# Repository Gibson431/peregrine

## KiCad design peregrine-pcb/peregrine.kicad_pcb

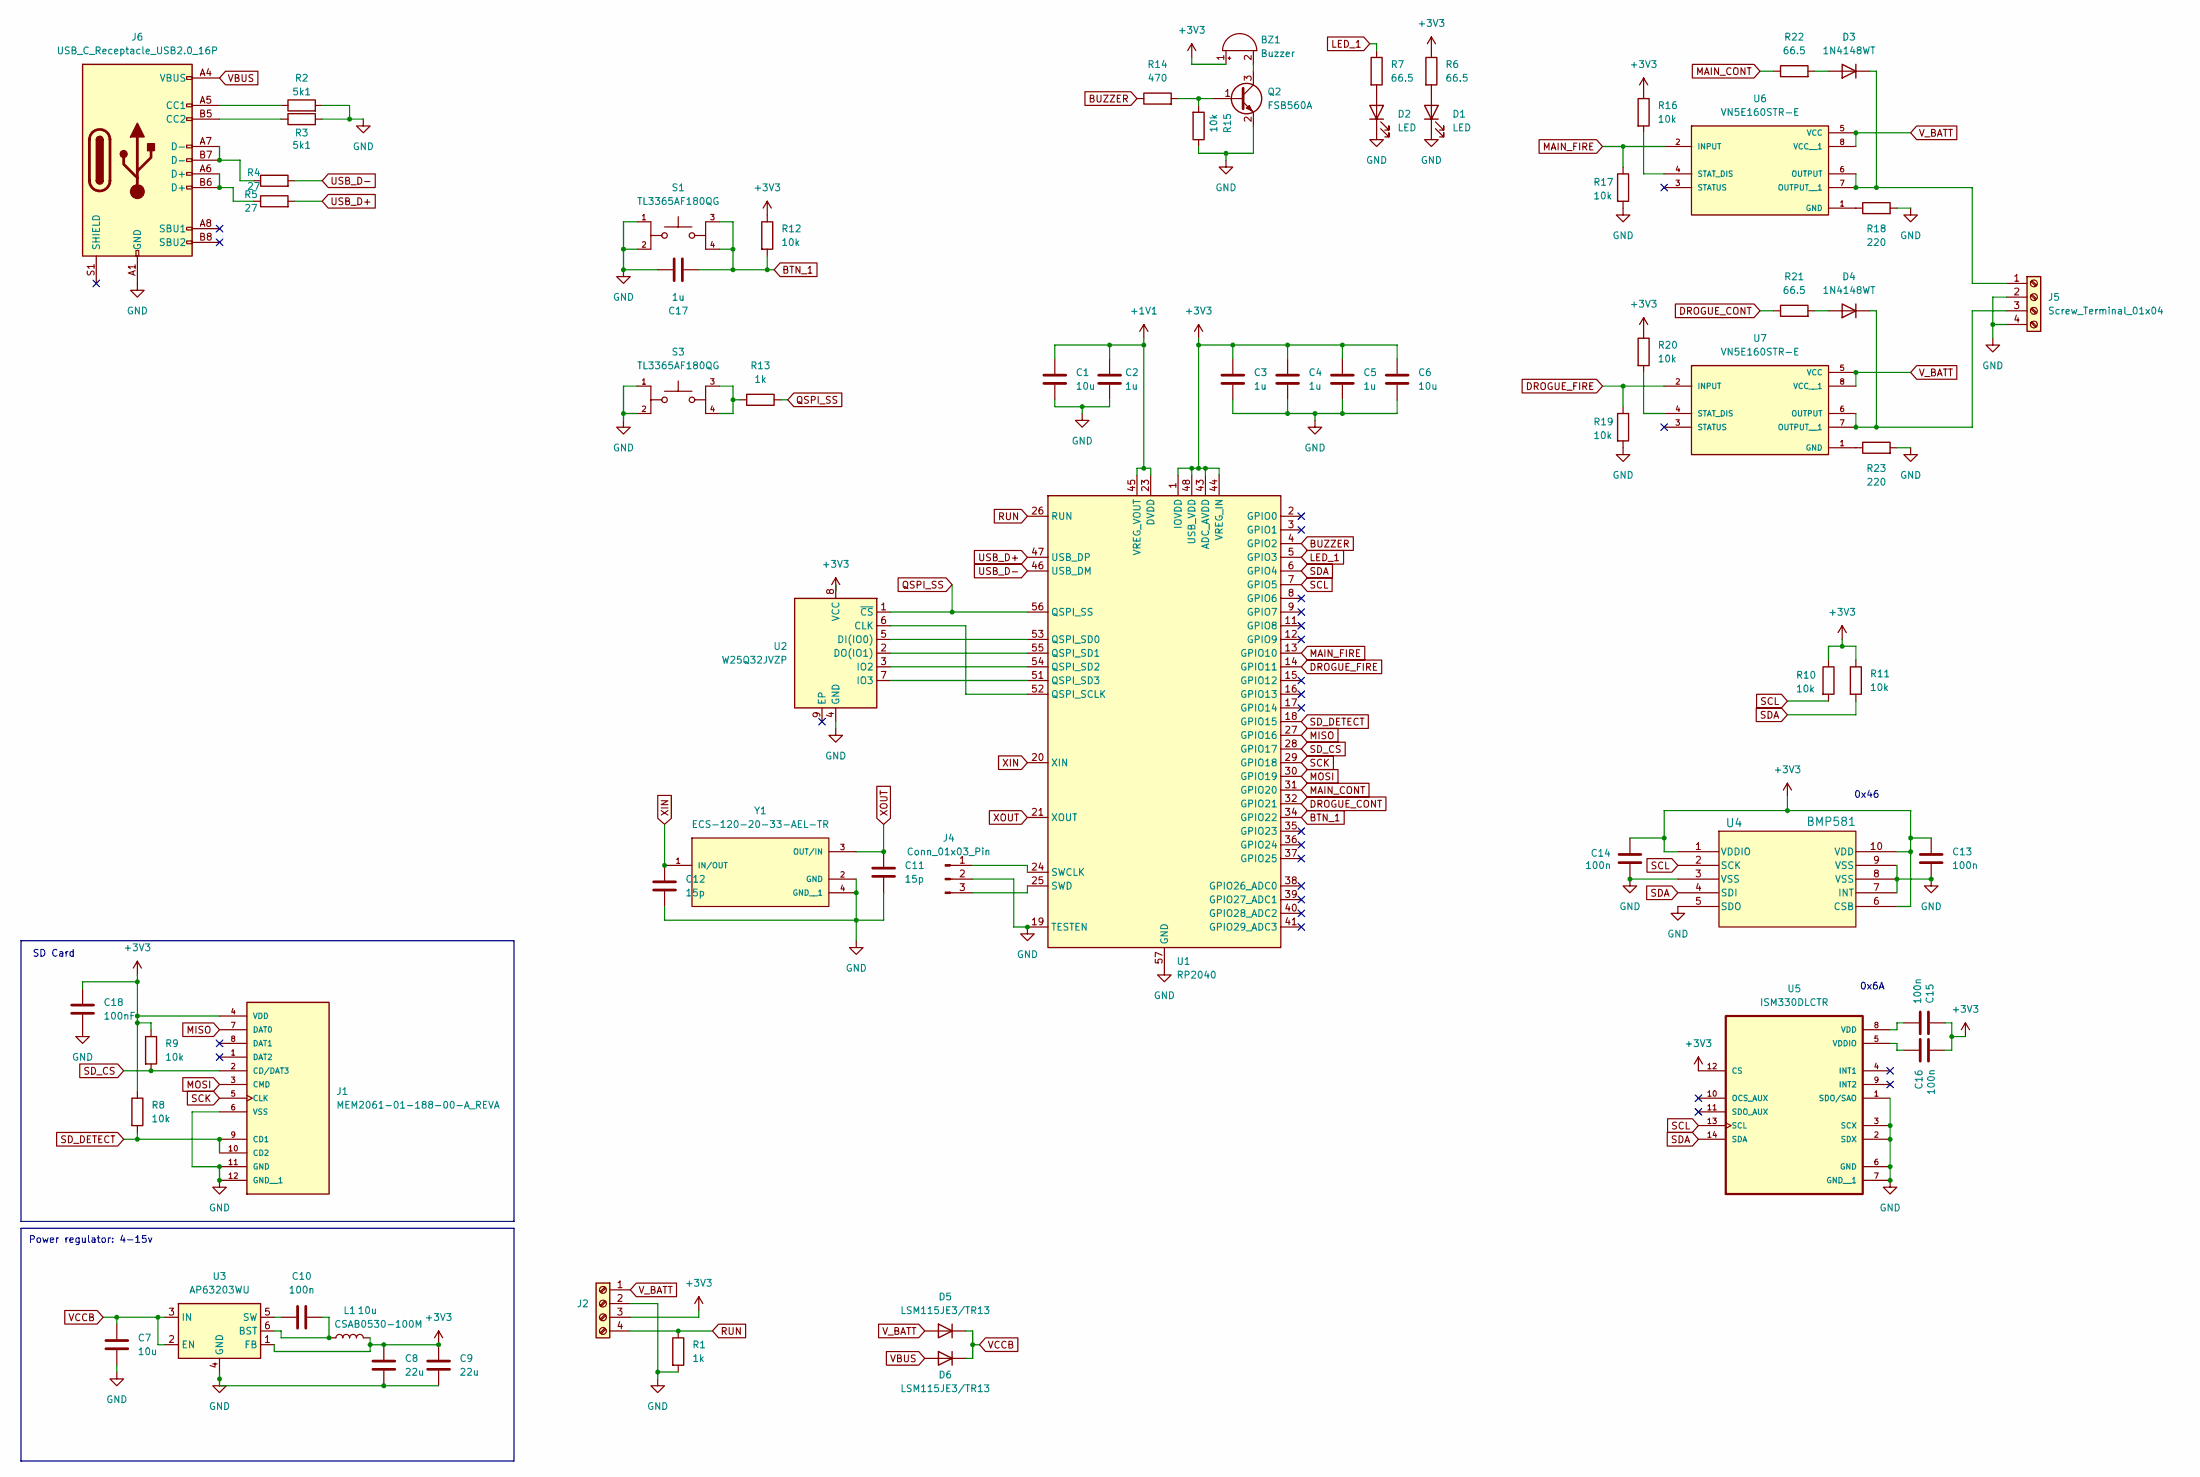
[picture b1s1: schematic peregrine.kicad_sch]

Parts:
BZ1: Buzzer; CUI_CBT-09427-SMT
C1, C6, C7: 10u; C_0603_1608Metric
C2, C3, C4, C5, C17: 1u; C_0603_1608Metric
C8, C9: 22u; C_0603_1608Metric
C10, C13, C14, C15, C16: 100n; C_0603_1608Metric
C11, C12: 15p; C_0603_1608Metric
C18: 100nF; C_0603_1608Metric
D1, D2: LED; LED_0603_1608Metric
D3, D4: 1N4148WT; D_SOD-523
D5, D6: LSM115JE3/TR13; DO-214BA_MCH
J1: MEM2061-01-188-00-A_REVA; GCT_MEM2061-01-188-00-A_REVA
J2, J5: Screw_Terminal_01x04; CONN4_500000G_AMP
J4: Conn_01x03_Pin; PinHeader_1x03_P2.54mm_Vertical
J6: USB_C_Receptacle_USB2.0_16P; USB_C_Receptacle_GCT_USB4105-xx-A_16P_TopMnt_Horizontal
L1: 10u; L_6.3x6.3_H3
Q2: FSB560A; SSOT3_3X1P5_ONS
R1, R13: 1k; R_0603_1608Metric
R2, R3: 5k1; R_0603_1608Metric
R4, R5: 27; R_0603_1608Metric
R6, R7, R21, R22: 66.5; R_0603_1608Metric
R8, R9, R10, R11, R12, R15, R16, R17, R19, R20: 10k; R_0603_1608Metric
R14: 470; R_0603_1608Metric
R18, R23: 220; R_0603_1608Metric
S1, S3: TL3365AF180QG; SW_TL3365AF180QG; PARTREV A
U1: RP2040; QFN-56-1EP_7x7mm_P0.4mm_EP3.2x3.2mm
U2: W25Q32JVZP; WSON-8-1EP_6x5mm_P1.27mm_EP3.4x4.3mm
U3: AP63203WU; TSOT-23-6
U4: BMP581; QFN10_BMP581_BOS
U5: ISM330DLCTR; PQFN50P250X300X86-14N; PARTREV 2
U6, U7: VN5E160STR-E; SOIC127P600X175-8N; PARTREV 3
Y1: ECS-120-20-33-AEL-TR; XTAL_ECS-120-20-33-AEL-TR

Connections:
+1V1: C1.1, C2.1, U1.23 (DVDD), U1.45 (VREG_VOUT), U1.50 (DVDD)
+3V3: BZ1.1 (+), C3.1, C4.1, C5.1, C6.1, C8.1, C9.1, C13.1, C14.1, C15.1, C16.2, C18.1, J1.4 (VDD), J2.3, L1.2, R6.1, R8.1, R9.1, R10.1, R11.1, R12.1, R16.1, R20.1, U1.1 (IOVDD), U1.10 (IOVDD), U1.22 (IOVDD), U1.33 (IOVDD), U1.42 (IOVDD), U1.43 (ADC_AVDD), U1.44 (VREG_IN), U1.48 (USB_VDD), U1.49 (IOVDD), U2.8 (VCC), U3.1 (FB), U4.1 (VDDIO), U4.6 (CSB), U4.10 (VDD), U5.12 (CS)
BTN_1: C17.1, R12.2, S1.3, S1.4, U1.34 (GPIO22)
BUZZER: R14.1, U1.4 (GPIO2)
DROGUE_CONT: R21.1, U1.32 (GPIO21)
DROGUE_FIRE: R19.1, U1.14 (GPIO11), U7.2 (INPUT)
GND: C1.2, C2.2, C3.2, C4.2, C5.2, C6.2, C7.2, C8.2, C9.2, C11.2, C12.2, C13.2, C14.2, C17.2, C18.2, D1.1 (K), D2.1 (K), J1.6 (VSS), J1.11 (GND), J1.12 (GND__1), J2.2, J4.2, J5.2, J5.4, J6.A1 (GND), J6.A12 (GND), J6.B1 (GND), J6.B12 (GND), Q2.2 (E), R1.2, R2.2, R3.2, R15.1, R17.2, R18.2, R19.2, R23.2, S1.1, S1.2, S3.1, S3.2, U1.19 (TESTEN), U1.57 (GND), U2.4 (GND), U3.4 (GND), U4.3 (VSS), U4.5 (SDO), U4.7 (INT), U4.8 (VSS), U4.9 (VSS), U5.1 (SDO/SAO), U5.2 (SDX), U5.3 (SCX), U5.6 (GND), U5.7 (GND__1), Y1.2 (GND), Y1.4 (GND__1)
LED_1: R7.1, U1.5 (GPIO3)
MAIN_CONT: R22.1, U1.31 (GPIO20)
MAIN_FIRE: R17.1, U1.13 (GPIO10), U6.2 (INPUT)
MISO: J1.7 (DAT0), U1.27 (GPIO16)
MOSI: J1.3 (CMD), U1.30 (GPIO19)
unnamed: BZ1.2 (-), Q2.3 (C)
unnamed: D1.2 (A), R6.2
unnamed: D2.2 (A), R7.2
unnamed: D3.2 (A), R22.2
unnamed: D3.1 (K), J5.1, U6.6 (OUTPUT), U6.7 (OUTPUT__1)
unnamed: D4.2 (A), R21.2
unnamed: D4.1 (K), J5.3, U7.6 (OUTPUT), U7.7 (OUTPUT__1)
unnamed: J4.1, U1.24 (SWCLK)
unnamed: J4.3, U1.25 (SWD)
unnamed: J6.A5 (CC1), R2.1
unnamed: J6.B5 (CC2), R3.1
unnamed: J6.A6 (D+), J6.B6 (D+), R5.1
unnamed: J6.A7 (D-), J6.B7 (D-), R4.1
unnamed: Q2.1 (B), R14.2, R15.2
unnamed: R13.2, S3.3, S3.4
unnamed: U1.52 (QSPI_SCLK), U2.6 (CLK)
unnamed: U1.53 (QSPI_SD0), U2.5 (DI(IO0))
unnamed: U1.55 (QSPI_SD1), U2.2 (DO(IO1))
unnamed: U1.54 (QSPI_SD2), U2.3 (IO2)
unnamed: U1.51 (QSPI_SD3), U2.7 (IO3)
unnamed: C10.2, L1.1, U3.6 (BST)
unnamed: C10.1, U3.5 (SW)
unnamed: C15.2, U5.8 (VDD)
unnamed: C16.1, U5.5 (VDDIO)
unnamed: R18.1, U6.1 (GND)
unnamed: R16.2, U6.4 (STAT_DIS)
unnamed: R23.1, U7.1 (GND)
unnamed: R20.2, U7.4 (STAT_DIS)
QSPI_SS: R13.1, U1.56 (QSPI_SS), U2.1 (~CS)
RUN: J2.4, R1.1, U1.26 (RUN)
SCK: J1.5 (CLK), U1.29 (GPIO18)
SCL: R10.2, U1.7 (GPIO5), U4.2 (SCK), U5.13 (SCL)
SDA: R11.2, U1.6 (GPIO4), U4.4 (SDI), U5.14 (SDA)
SD_CS: J1.2 (CD/DAT3), R9.2, U1.28 (GPIO17)
SD_DETECT: J1.9 (CD1), J1.10 (CD2), R8.2, U1.18 (GPIO15)
USB_D+: R5.2, U1.47 (USB_DP)
USB_D-: R4.2, U1.46 (USB_DM)
VBUS: D6.2 (A), J6.A4 (VBUS), J6.A9 (VBUS), J6.B4 (VBUS), J6.B9 (VBUS)
VCCB: C7.1, D5.1 (K), D6.1 (K), U3.2 (EN), U3.3 (IN)
V_BATT: D5.2 (A), J2.1, U6.5 (VCC), U6.8 (VCC__1), U7.5 (VCC), U7.8 (VCC__1)
XIN: C12.1, U1.20 (XIN), Y1.1 (IN/OUT)
XOUT: C11.1, U1.21 (XOUT), Y1.3 (OUT/IN)

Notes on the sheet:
SD Card
0x46
Power regulator: 4-15v
0x6A

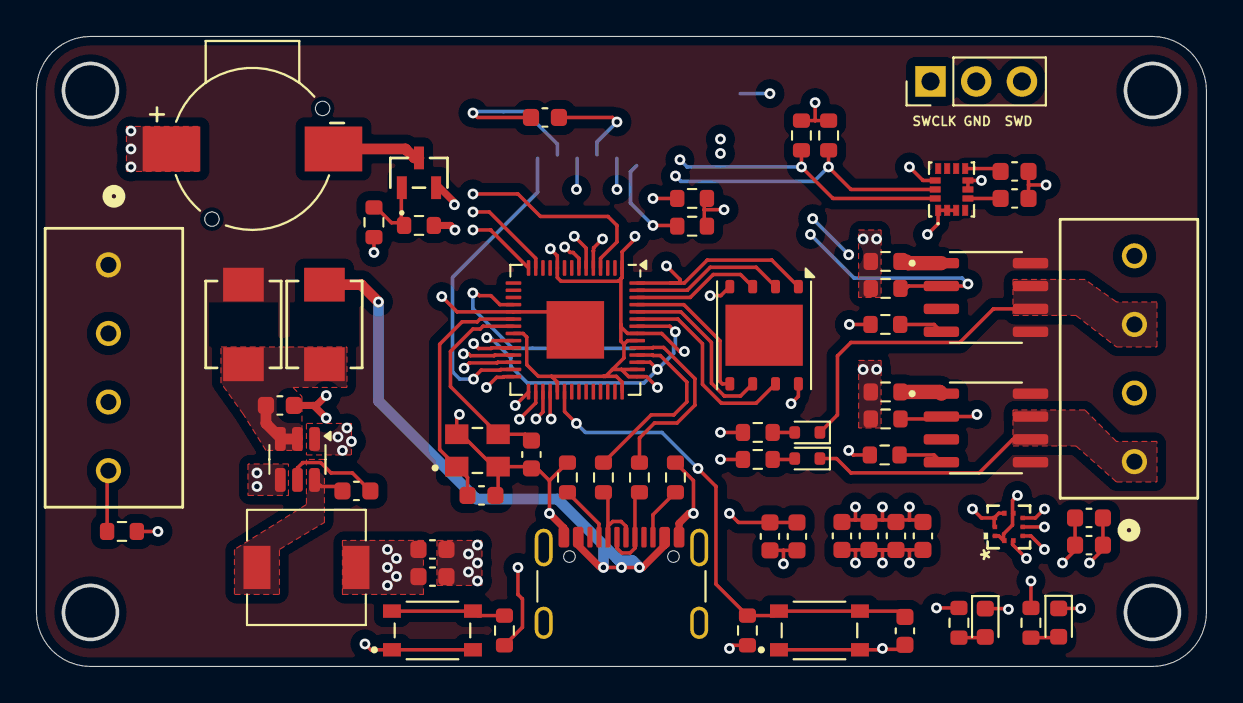
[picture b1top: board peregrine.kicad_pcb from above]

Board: 4 copper layers, 64.9 x 34.9 mm, 65 parts (1 on the bottom side), 54 nets.

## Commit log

2024-09-08 initial work
2024-09-08 working scaffold for data transfer
2024-09-16 first pass for pcb
2024-09-16 mvp for embassy framework
2024-09-25 rs progress + ardu ccls ignore
